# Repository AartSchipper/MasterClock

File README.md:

MasterClock
===========

Arduino based master clock for slave clocks. 
--------------------------------------------

* Minute or second impulses. 
* DCF-77 as a time reference. 
* Siderial, lockal or UTC time. 

This is an Arduino project that runs up to two (sets of-) slave clocks showing different types of time. It was created for the 24h second impulse clocks of the Old Leiden Observatory. 

The project consists of specially created hardware, akin to an Arduino Uno with an xtal and some interfaces, and an Arduino based firmware. The firmware is based on the DCF library and examples by: https://github.com/udoklein/dcf77, Copyright 2016 Udo Klein, GPL

Aart, 04-2020

Hardware layout
---------------

The hardware consists of an low-current 24V H-bridge per clock, the processor, a DCF receiver, a power supply and some auxilary circuits. 

A red/green duo led shows the DCF pulses and if the clock is currently synced to dcf. An extra provision is made to power and switch the lamps (24V / 12W) in the clock dials. Care was taken to use only lineair regulators and just one lighly loaded electrolitic capacitor for longelivity. The regulators are mounted on the aluminium base for cooling. 

The firmware should run on almost any Arduino compatible hardware _with a crystal_. A resonator might cause problems with the DCF library, see: https://github.com/udoklein/dcf77 

There is a standard six pin UART interface both for programming using the bootloader, and setting using a terminal. There is a jumper to disable the reset of the uC, to avoid nuisance resets in normal use. 

A known omission in the current hardware is a pull-down resistor on the gate of the MOSFET for the lights. 

The design was made in KiCad. Gerbers and a PDF of the circuits are provided.  

Firmware layout
---------------

The Dial class contains all functions related to a dial. 
dail1 & dail2 are instances of this class. 

Every millisecond sample_input_pin() is called by the DCF library.   
In this routine also Dial::DialSR(), the dial Service Routine is called to see if a puls needs to be started or stopped.   

The rest of the program runs in the main loop and is not time critical. In this loop: 
* powerCheck() stops the dails in case of power loss and stores the positions in EEPROM, so the clocks can continue automatically when power returns. 
* Check_serial_input() Handles the terminal for debugging and synchonizing the dials. 
* Dial::DoCorrection() Handles synchronising the dials to DCF, or running the dial at the correct rate in case the DCF signal is lost. 

Terminal
--------

The firmware has a simple provision for reading the time and setting the current position of the hands on the dials using the terminal:

---

Klok impuls gever 2.40 WLS, Aart 2020
> Status: 

> 109 times restarted

>Longitude: 4.46

> UTC time:       synced: Monday    2020-04-13 10:51:17 
> Local siderial: 0:37;26 
> Local time:     synced: Monday    2020-04-13 12:51:17 UTC+02

> Dial 1: Type: 24h, seconds, siderial. Position: 0:37;26 correction: 0 ms/impuls

> To set dial 1: 1hhmmss, dial 2: 2hhmmss

---

Dial type, time type and Longitude are all compile time settings. If the dial positions are not set 0:00;00 is assumed at first startup. 

Typical behaviour
-----------------

Assuming the dail positions were correct during shutdown: 
* After startup the dials run in the default speed of the time type until the DCF library is synced.  
* When the library is synced the led turns green and the hands are moved to the correct position (minute impulse dials) or stopped (second impulse dials) to wait until the correct time to start. 

Small deviations up to six minutes are corrected by making the pauses between impulses slightly longer or shorter.

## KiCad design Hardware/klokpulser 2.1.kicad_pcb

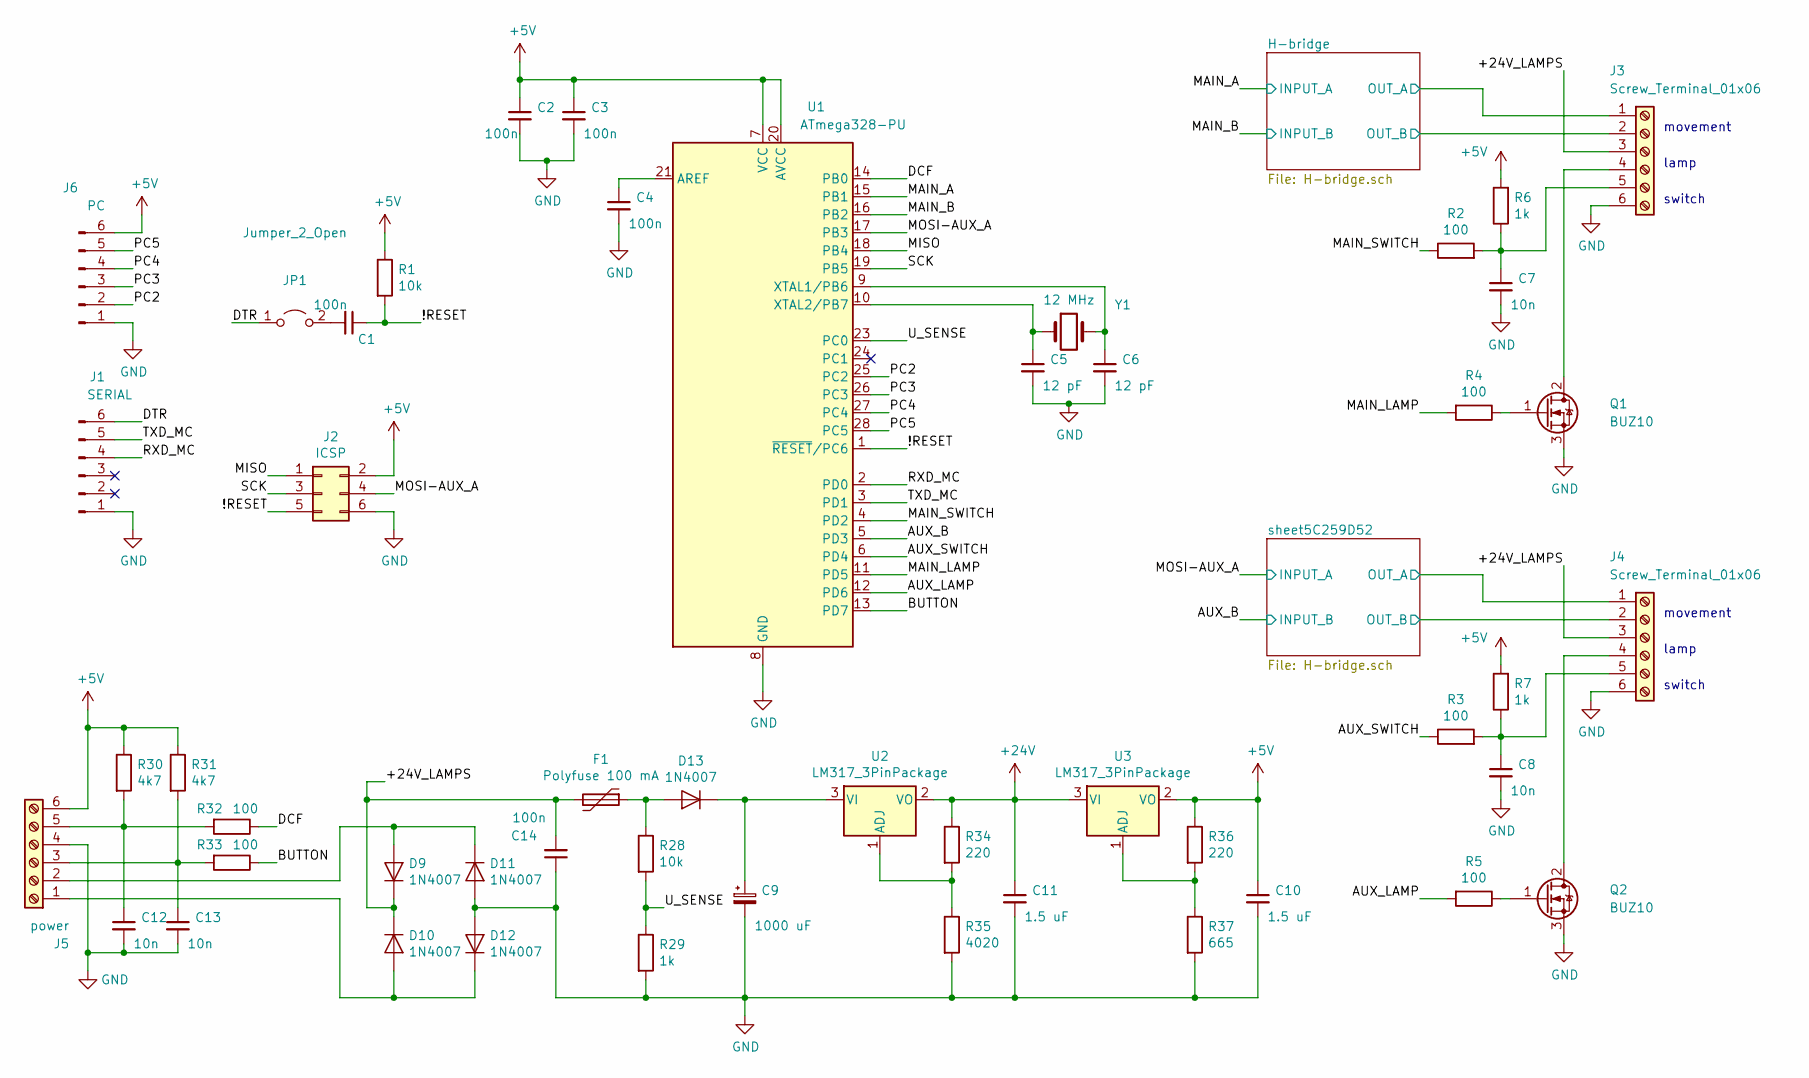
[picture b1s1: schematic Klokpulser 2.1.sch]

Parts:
C1, C2, C3, C4, C14: 100n; C_Rect_L7.0mm_W3.5mm_P2.50mm_P5.00mm
C5, C6: 12 pF; C_Rect_L7.0mm_W2.0mm_P5.00mm
C7, C8, C12, C13: 10n; C_Rect_L7.0mm_W3.5mm_P2.50mm_P5.00mm
C9: 1000 uF; CP_Radial_D16.0mm_P7.50mm
C10, C11: 1.5 uF; C_Rect_L7.0mm_W6.0mm_P5.00mm
D9, D10, D11, D12, D13: 1N4007; D_DO-41_SOD81_P10.16mm_Horizontal
F1: Polyfuse 100 mA; RV_Disc_D7mm_W3.4mm_P5mm
J1: SERIAL; PinHeader_1x06_P2.54mm_Vertical
J2: ICSP; PinHeader_2x03_P2.54mm_Vertical
J3, J4: Screw_Terminal_01x06; PhoenixContact_MC_1,5_6-G-3.81_1x06_P3.81mm_Horizontal
J5: power; PhoenixContact_MC_1,5_6-G-3.81_1x06_P3.81mm_Horizontal
J6: PC; PinHeader_1x06_P2.54mm_Vertical
JP1: Jumper_2_Open; PinSocket_1x02_P2.54mm_Vertical
Q1, Q2: BUZ10; TO-220-3_Vertical
R1, R28: 10k; R_Axial_DIN0207_L6.3mm_D2.5mm_P10.16mm_Horizontal
R2, R3, R4, R5, R32, R33: 100; R_Axial_DIN0207_L6.3mm_D2.5mm_P10.16mm_Horizontal
R6, R7, R29: 1k; R_Axial_DIN0207_L6.3mm_D2.5mm_P10.16mm_Horizontal
R30, R31: 4k7; R_Axial_DIN0207_L6.3mm_D2.5mm_P10.16mm_Horizontal
R34, R36: 220; R_Axial_DIN0207_L6.3mm_D2.5mm_P10.16mm_Horizontal
R35: 4020; R_Axial_DIN0207_L6.3mm_D2.5mm_P10.16mm_Horizontal
R37: 665; R_Axial_DIN0207_L6.3mm_D2.5mm_P10.16mm_Horizontal
U1: ATmega328-PU; DIP-28_W7.62mm
U2, U3: LM317_3PinPackage; TO-220-3_Horizontal_TabDown
Y1: 12 MHz; Crystal_HC49-U_Vertical

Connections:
+5V: C2.1, C3.1, C10.1, J2.2, J5.6, J6.6, R1.1, R6.2, R7.2, R30.1, R31.1, R36.1, U1.7 (VCC), U1.20 (AVCC), U3.2 (VO)
+24V: C11.1, R34.1, U2.2 (VO), U3.3 (VI); also elsewhere on the board
/!RESET: C1.1, J2.5, R1.2, U1.1 (~RESET~/PC6)
/+24V_LAMPS: C14.2, D9.1 (K), D10.1 (K), F1.2, J3.3, J4.3
/AUX_B: U1.5 (PD3); also elsewhere on the board
/AUX_LAMP: R5.2, U1.12 (PD6)
/AUX_SWITCH: R3.1, U1.6 (PD4)
/BUTTON: R33.1, U1.13 (PD7)
/DCF: R32.1, U1.14 (PB0)
/DTR: J1.6, JP1.1 (A)
/H-bridge/OUT_A: J3.1; also elsewhere on the board
/H-bridge/OUT_B: J3.2; also elsewhere on the board
/MAIN_A: U1.15 (PB1); also elsewhere on the board
/MAIN_B: U1.16 (PB2); also elsewhere on the board
/MAIN_LAMP: R4.2, U1.11 (PD5)
/MAIN_SWITCH: R2.1, U1.4 (PD2)
/MISO: J2.1, U1.18 (PB4)
/MOSI-AUX_A: J2.4, U1.17 (PB3); also elsewhere on the board
/PC2: J6.2, U1.25 (PC2)
/PC3: J6.3, U1.26 (PC3)
/PC4: J6.4, U1.27 (PC4)
/PC5: J6.5, U1.28 (PC5)
/RXD_MC: J1.4, U1.2 (PD0)
/SCK: J2.3, U1.19 (PB5)
/TXD_MC: J1.5, U1.3 (PD1)
/U_SENSE: R28.2, R29.1, U1.23 (PC0)
/sheet5C259D52/OUT_A: J4.1; also elsewhere on the board
/sheet5C259D52/OUT_B: J4.2; also elsewhere on the board
GND: C2.2, C3.2, C4.2, C5.2, C6.2, C7.2, C8.2, C9.2, C10.2, C11.2, C12.2, C13.2, C14.1, D11.2 (A), D12.2 (A), J1.1, J2.6, J3.6, J4.6, J5.4, J6.1, Q1.3 (S), Q2.3 (S), R29.2, R35.2, R37.2, U1.8 (GND), U1.22 (GND); also elsewhere on the board
unnamed: C1.2, JP1.2 (B)
unnamed: C4.1, U1.21 (AREF)
unnamed: C5.1, U1.10 (XTAL2/PB7), Y1.1
unnamed: C6.1, U1.9 (XTAL1/PB6), Y1.2
unnamed: C7.1, J3.5, R2.2, R6.1
unnamed: C8.1, J4.5, R3.2, R7.1
unnamed: C9.1, D13.1 (K), U2.3 (VI)
unnamed: C12.1, J5.5, R30.2, R32.2
unnamed: C13.1, J5.3, R31.2, R33.2
unnamed: D10.2 (A), D12.1 (K), J5.1
unnamed: D9.2 (A), D11.1 (K), J5.2
unnamed: D13.2 (A), F1.1, R28.1
unnamed: J3.4, Q1.2 (D)
unnamed: J4.4, Q2.2 (D)
unnamed: Q1.1 (G), R4.1
unnamed: Q2.1 (G), R5.1
unnamed: R34.2, R35.1, U2.1 (ADJ)
unnamed: R36.2, R37.1, U3.1 (ADJ)

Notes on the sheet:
movement
lamp
switch

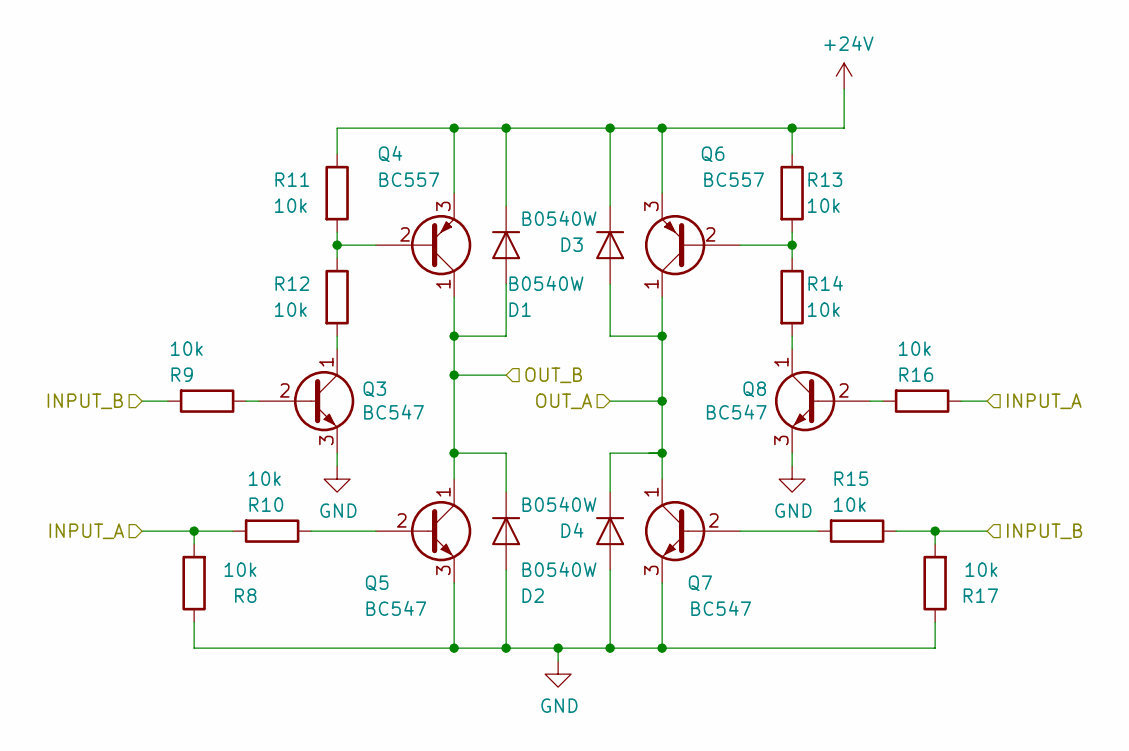
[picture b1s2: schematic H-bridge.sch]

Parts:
D1, D2, D3, D4: B0540W; D_DO-41_SOD81_P10.16mm_Horizontal
Q3, Q5, Q7, Q8: BC547; TO-92_Inline
Q4, Q6: BC557; TO-92_Inline
R8, R9, R10, R11, R12, R13, R14, R15, R16, R17: 10k; R_Axial_DIN0207_L6.3mm_D2.5mm_P10.16mm_Horizontal

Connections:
+24V: D1.1 (K), D3.1 (K), Q4.3 (E), Q6.3 (E), R11.1, R13.1; also elsewhere on the board
/H-bridge/OUT_A: D3.2 (A), D4.1 (K), Q6.1 (C), Q7.1 (C); also elsewhere on the board
/H-bridge/OUT_B: D1.2 (A), D2.1 (K), Q4.1 (C), Q5.1 (C); also elsewhere on the board
/MAIN_A: R8.2, R10.2, R16.1; also elsewhere on the board
/MAIN_B: R9.2, R15.1, R17.2; also elsewhere on the board
GND: D2.2 (A), D4.2 (A), Q3.3 (E), Q5.3 (E), Q7.3 (E), Q8.3 (E), R8.1, R17.1; also elsewhere on the board
unnamed: Q3.1 (C), R12.2
unnamed: Q3.2 (B), R9.1
unnamed: Q4.2 (B), R11.2, R12.1
unnamed: Q5.2 (B), R10.1
unnamed: Q6.2 (B), R13.2, R14.1
unnamed: Q7.2 (B), R15.2
unnamed: Q8.1 (C), R14.2
unnamed: Q8.2 (B), R16.2

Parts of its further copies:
D5, D6, D7, D8: B0540W; D_DO-41_SOD81_P10.16mm_Horizontal
Q9, Q11, Q13, Q14: BC547; TO-92_Inline
Q10, Q12: BC557; TO-92_Inline
R18, R19, R20, R21, R22, R23, R24, R25, R26, R27: 10k; R_Axial_DIN0207_L6.3mm_D2.5mm_P10.16mm_Horizontal

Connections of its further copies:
+24V: D5.1 (K), D7.1 (K), Q10.3 (E), Q12.3 (E), R21.1, R23.1; also elsewhere on the board
/AUX_B: R19.2, R25.1, R27.2; also elsewhere on the board
/MOSI-AUX_A: R18.2, R20.2, R26.1; also elsewhere on the board
/sheet5C259D52/OUT_A: D7.2 (A), D8.1 (K), Q12.1 (C), Q13.1 (C); also elsewhere on the board
/sheet5C259D52/OUT_B: D5.2 (A), D6.1 (K), Q10.1 (C), Q11.1 (C); also elsewhere on the board
GND: D6.2 (A), D8.2 (A), Q9.3 (E), Q11.3 (E), Q13.3 (E), Q14.3 (E), R18.1, R27.1; also elsewhere on the board
unnamed: Q9.1 (C), R22.2
unnamed: Q9.2 (B), R19.1
unnamed: Q10.2 (B), R21.2, R22.1
unnamed: Q11.2 (B), R20.1
unnamed: Q12.2 (B), R23.2, R24.1
unnamed: Q13.2 (B), R25.2
unnamed: Q14.1 (C), R24.2
unnamed: Q14.2 (B), R26.2

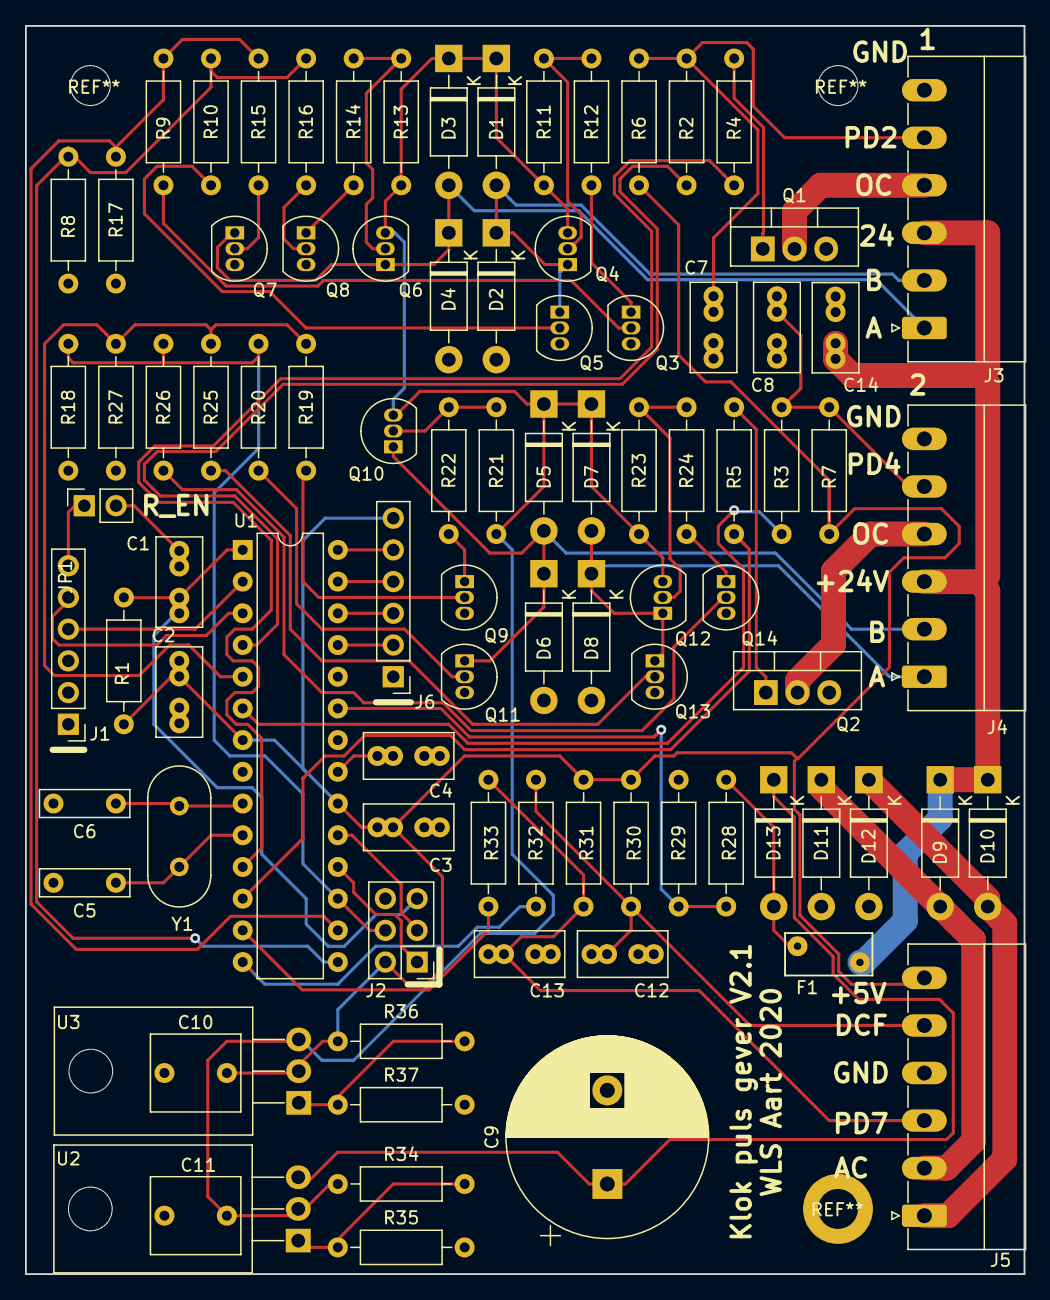
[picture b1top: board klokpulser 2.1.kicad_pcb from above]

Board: 2 copper layers, 80.0 x 100.0 mm, 90 parts (0 on the bottom side), 63 nets.

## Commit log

2020-03-08 V2.4. Replace powercheck, add local DST, refactoring
2020-03-14 Correct types
2020-04-09 Fix 12h dials
2020-04-09 Fix variable type error
2020-04-12 Set max offset to 0 for SEC24
2020-04-13 Add readme
2020-04-13 Fix readme typo's
2020-04-13 Add hardware
2020-04-13 Change minute sync
